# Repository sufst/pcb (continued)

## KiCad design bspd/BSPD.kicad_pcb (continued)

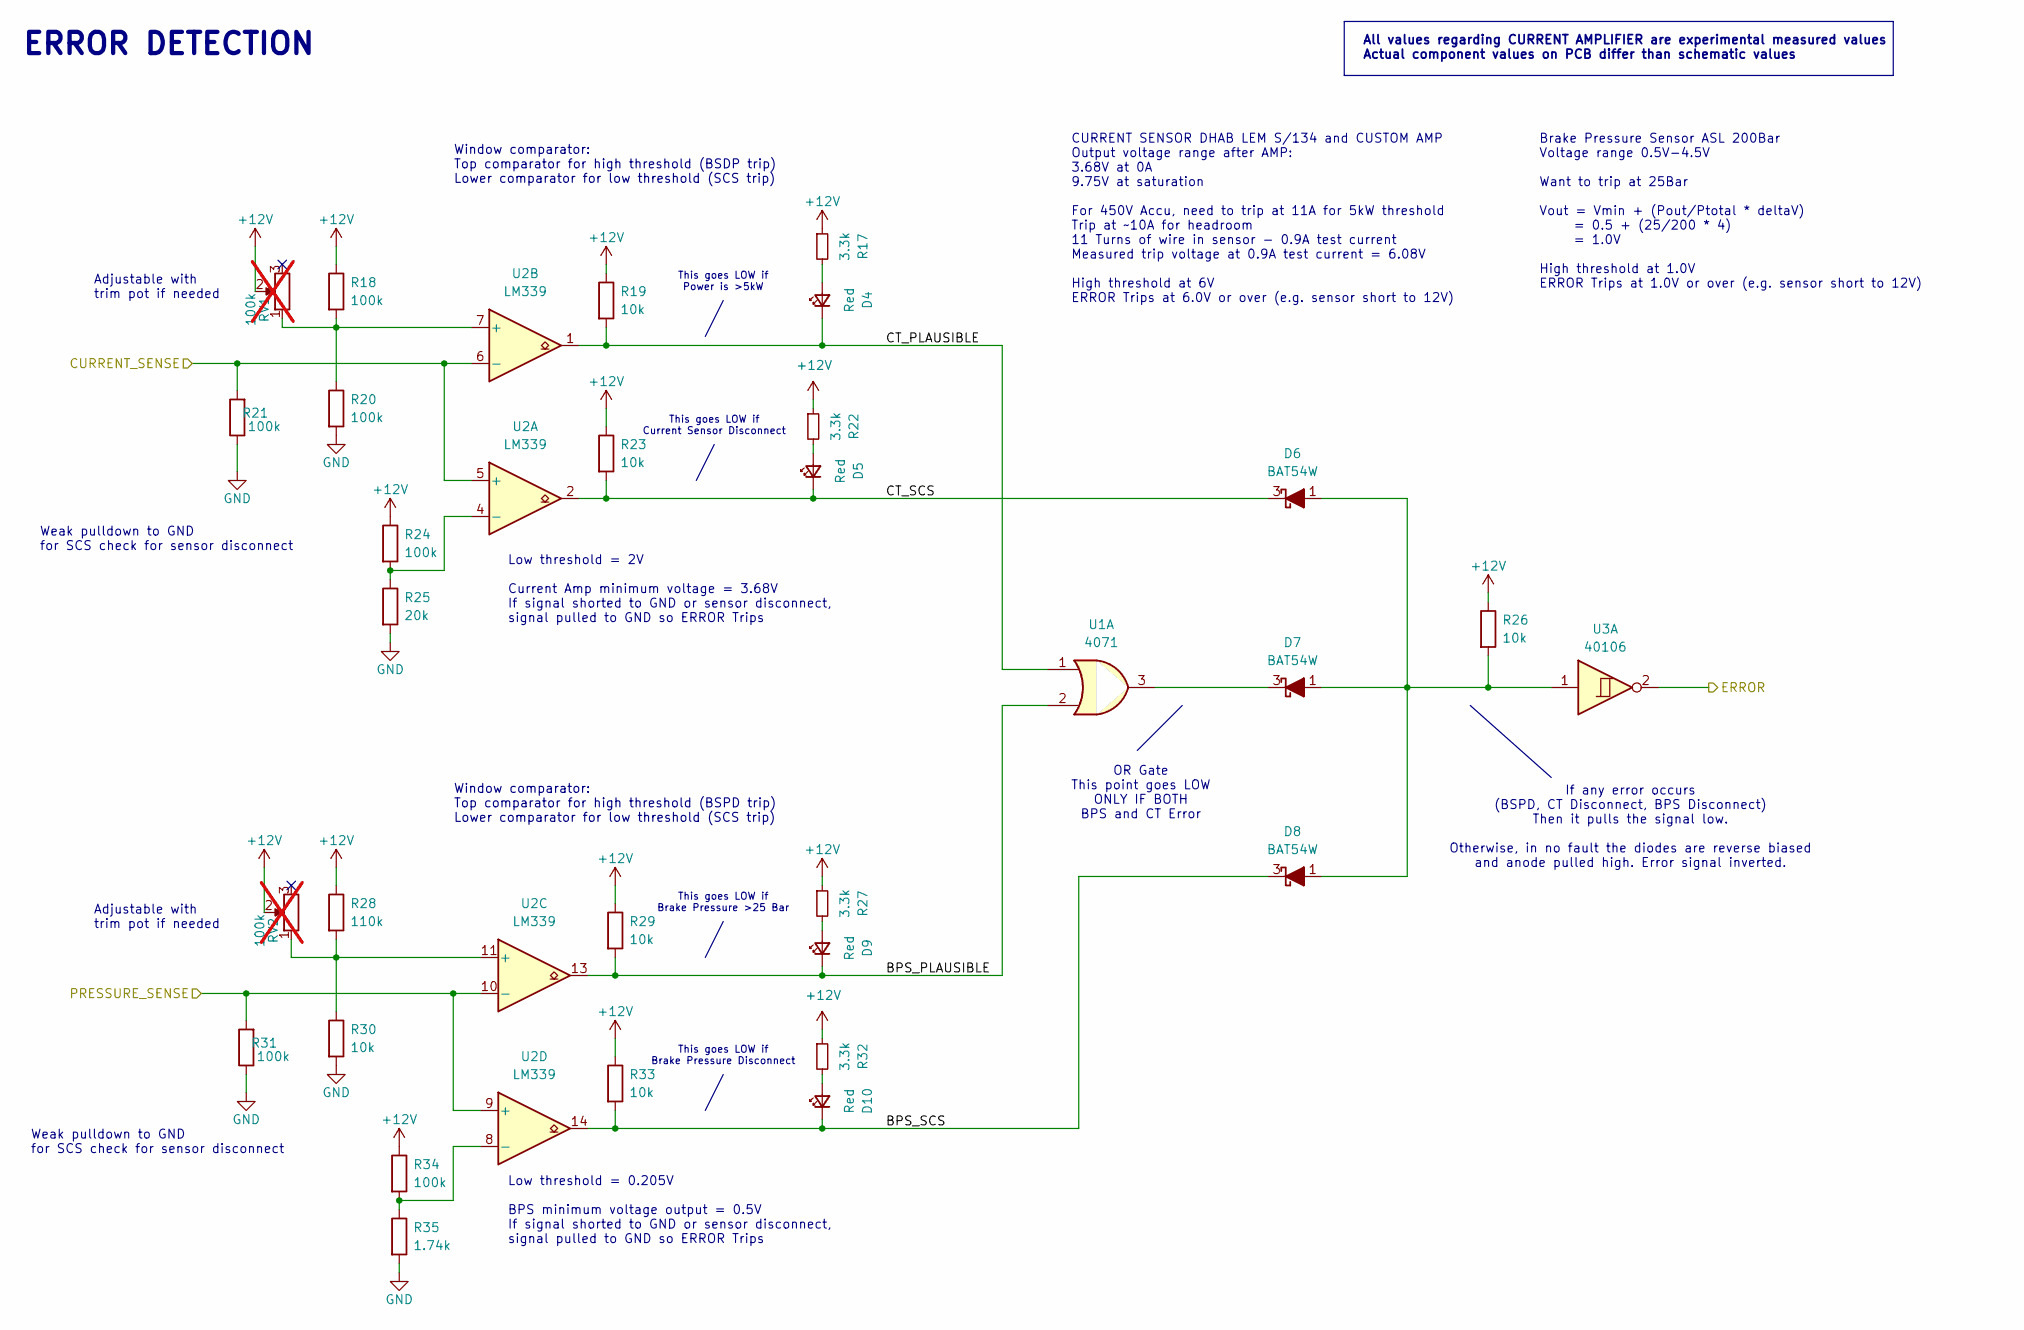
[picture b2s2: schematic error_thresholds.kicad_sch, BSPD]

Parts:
D4, D5, D9, D10: Red; LED_0603_1608Metric
D6, D7, D8: BAT54W; SOT-323_SC-70
R17, R22, R27, R32: 3.3k; R_0603_1608Metric
R18: 100k; R_0603_1608Metric; Mouser Part Number 603-RT0603FRE072K7L
R19, R23, R26, R29, R33: 10k; R_0603_1608Metric
R20, R24, R34: 100k; R_0603_1608Metric; Mouser Part Number 603-RT0603FRD078K2L
R21, R31: 100k; R_0603_1608Metric
R25: 20k; R_0603_1608Metric
R28: 110k; R_0603_1608Metric; Mouser Part Number 603-RT0603FRE072K7L
R30: 10k; R_0603_1608Metric; Mouser Part Number 603-RT0603FRD078K2L
R35: 1.74k; R_0603_1608Metric
RV1, RV2: 100k; Potentiometer_Bourns_3266W_Vertical; not fitted
U1: 4071; SOIC-14_3.9x8.7mm_P1.27mm
U2: LM339; SOIC-14_3.9x8.7mm_P1.27mm
U3: 40106; SOIC-14_3.9x8.7mm_P1.27mm

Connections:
+12V: R17.1, R18.1, R19.1, R22.1, R23.1, R24.1, R26.1, R27.1, R28.1, R29.1, R32.1, R33.1, R34.1, RV1.2, RV2.2; also elsewhere on the board
/BPS_SIG: R31.2, U2.9 (+), U2.10 (-); also elsewhere on the board
/CT_SIG: R21.2, U2.5 (+), U2.6 (-); also elsewhere on the board
/Error Thresholds/BPS_PLAUSIBLE: D9.1 (K), R29.2, U1.2, U2.13
/Error Thresholds/BPS_SCS: D8.3 (K), D10.1 (K), R33.2, U2.14
/Error Thresholds/CT_PLAUSIBLE: D4.1 (K), R19.2, U1.1, U2.1
/Error Thresholds/CT_SCS: D5.1 (K), D6.3 (K), R23.2, U2.2
/Error Thresholds/ERROR: U3.2; also elsewhere on the board
GND: R20.2, R21.1, R25.2, R30.2, R31.1, R35.2; also elsewhere on the board
unnamed: D4.2 (A), R17.2
unnamed: D5.2 (A), R22.2
unnamed: D6.1 (A), D7.1 (A), D8.1 (A), R26.2, U3.1
unnamed: D7.3 (K), U1.3
unnamed: D9.2 (A), R27.2
unnamed: D10.2 (A), R32.2
unnamed: R24.2, R25.1, U2.4 (-)
unnamed: R18.2, R20.1, RV1.1, U2.7 (+)
unnamed: R28.2, R30.1, RV2.1, U2.11 (+)
unnamed: R34.2, R35.1, U2.8 (-)

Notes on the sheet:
ERROR DETECTION
Low threshold = 0.205V BPS minimum voltage output = 0.5V If signal shorted to GND or sensor disconnect, signal pulled to GND so ERROR Trips
Low threshold = 2V Current Amp minimum voltage = 3.68V If signal shorted to GND or sensor disconnect, signal pulled to GND so ERROR Trips
OR Gate This point goes LOW ONLY IF BOTH BPS and CT Error
Window comparator: Top comparator for high threshold (BSPD trip) Lower comparator for low threshold (SCS trip)
All values regarding CURRENT AMPLIFIER are experimental measured values Actual component values on PCB differ than schematic values
Weak pulldown to GND for SCS check for sensor disconnect
This goes LOW if Power is >5kW
Window comparator: Top comparator for high threshold (BSDP trip) Lower comparator for low threshold (SCS trip)
CURRENT SENSOR DHAB LEM S/134 and CUSTOM AMP Output voltage range after AMP: 3.68V at 0A 9.75V at saturation For 450V Accu, need to trip at 11A for 5kW threshold Trip at ~10A for headroom 11 Turns of wire in sensor - 0.9A test current Measured trip voltage at 0.9A test current = 6.08V High threshol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
This goes LOW if Current Sensor Disconnect
Adjustable with trim pot if needed
If any error occurs (BSPD, CT Disconnect, BPS Disconnect) Then it pulls the signal low. Otherwise, in no fault the diodes are reverse biased and anode pulled high. Error signal inverted.
Brake Pressure Sensor ASL 200Bar Voltage range 0.5V-4.5V Want to trip at 25Bar Vout = Vmin + (Pout/Ptotal * deltaV) = 0.5 + (25/200 * 4) = 1.0V High threshold at 1.0V ERROR Trips at 1.0V or over (e.g. sensor short to 12V)
This goes LOW if Brake Pressure Disconnect
This goes LOW if Brake Pressure >25 Bar

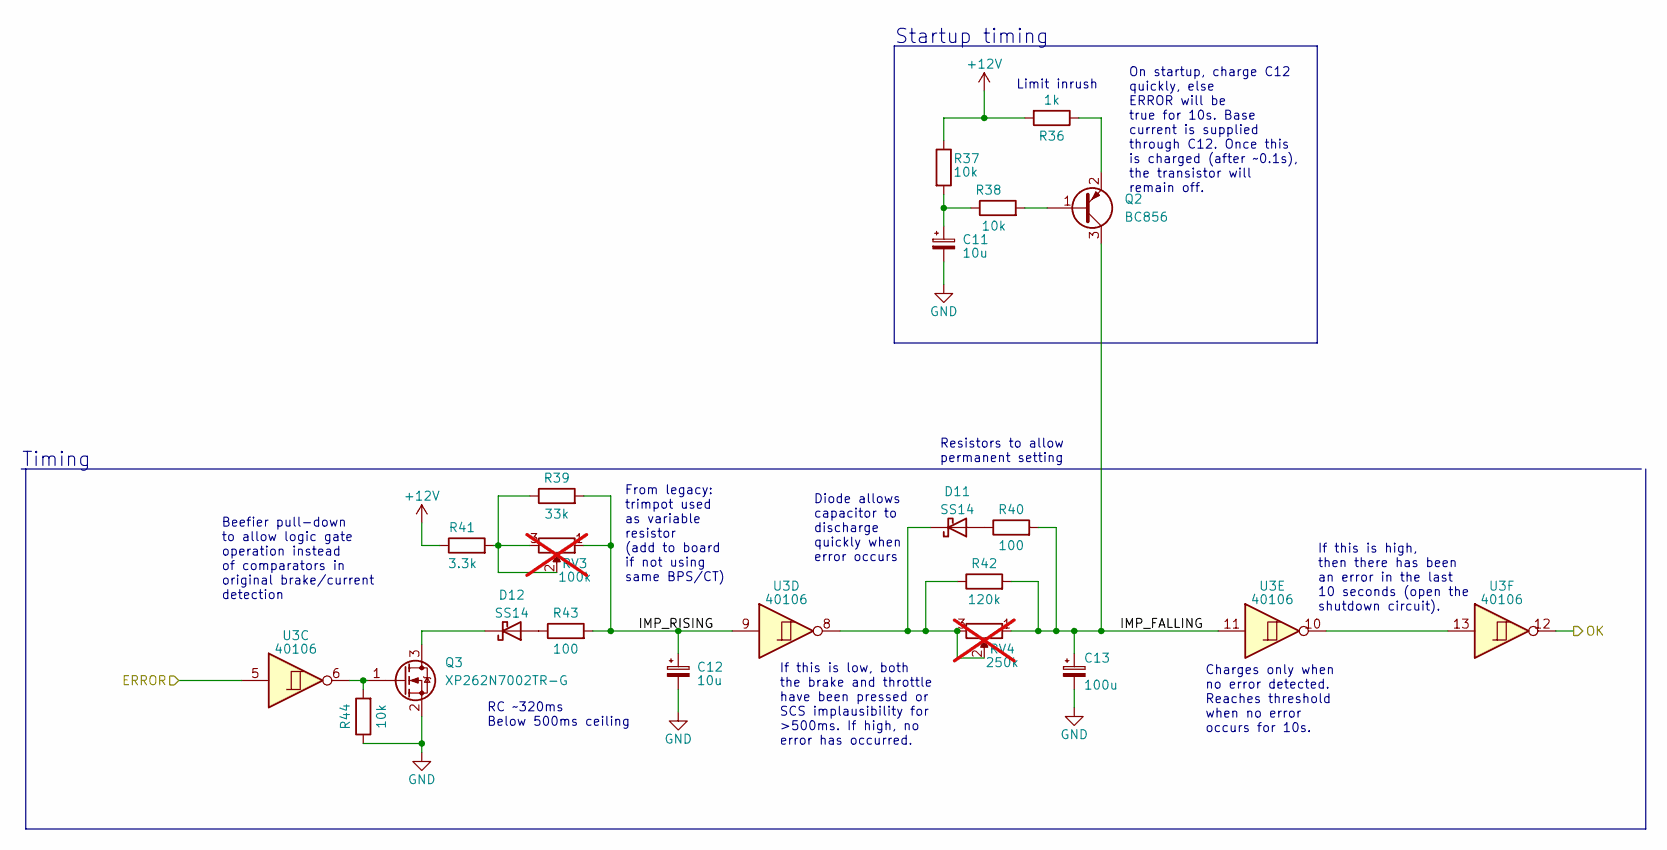
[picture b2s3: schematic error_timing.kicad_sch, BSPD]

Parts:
C11, C12: 10u; CP_Radial_D5.0mm_P2.00mm
C13: 100u; CP_Radial_D5.0mm_P2.00mm
D11, D12: SS14; D_SMA
Q2: BC856; SOT-23
Q3: XP262N7002TR-G; SOT-23
R36: 1k; R_0603_1608Metric
R37, R38, R44: 10k; R_0603_1608Metric
R39: 33k; R_0603_1608Metric; Mouser Part Number 603-RT0603FRE0733KL
R40, R43: 100; R_0603_1608Metric; Mouser Part Number 603-RT0603FRE07100RL
R41: 3.3k; R_0603_1608Metric
R42: 120k; R_0603_1608Metric
RV3: 100k; Potentiometer_Bourns_3266W_Vertical; not fitted
RV4: 250k; Potentiometer_Bourns_3266W_Vertical; not fitted
U3: 40106; SOIC-14_3.9x8.7mm_P1.27mm

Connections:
+12V: R36.2, R37.1, R41.1; also elsewhere on the board
/Error Thresholds/ERROR: U3.5; also elsewhere on the board
/Error Timing/IMP_FALLING: C13.1, Q2.3 (C), R40.2, R42.2, RV4.1, U3.11
/Error Timing/IMP_RISING: C12.1, R39.2, R43.2, RV3.1, U3.9
/Error Timing/OK: U3.12; also elsewhere on the board
GND: C11.2, C12.2, C13.2, Q3.2 (S), R44.1; also elsewhere on the board
unnamed: C11.1, R37.2, R38.1
unnamed: D11.2 (A), R40.1
unnamed: D11.1 (K), R42.1, RV4.2, RV4.3, U3.8
unnamed: D12.2 (A), R43.1
unnamed: D12.1 (K), Q3.3 (D)
unnamed: Q2.1 (B), R38.2
unnamed: Q2.2 (E), R36.1
unnamed: Q3.1 (G), R44.2, U3.6
unnamed: R39.1, R41.2, RV3.2, RV3.3
unnamed: U3.10, U3.13

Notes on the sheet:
Resistors to allow permanent setting
From legacy: trimpot used as variable resistor (add to board if not using same BPS/CT)
If this is low, both the brake and throttle have been pressed or SCS implausibility for >500ms. If high, no error has occurred.
Charges only when no error detected. Reaches threshold when no error occurs for 10s.
On startup, charge C12 quickly, else ERROR will be true for 10s. Base current is supplied through C12. Once this is charged (after ~0.1s), the transistor will remain off.
Limit inrush
Timing
RC ~320ms Below 500ms ceiling
Startup timing
If this is high, then there has been an error in the last 10 seconds (open the shutdown circuit).
Beefier pull-down to allow logic gate operation instead of comparators in original brake/current detection
Diode allows capacitor to discharge quickly when error occurs

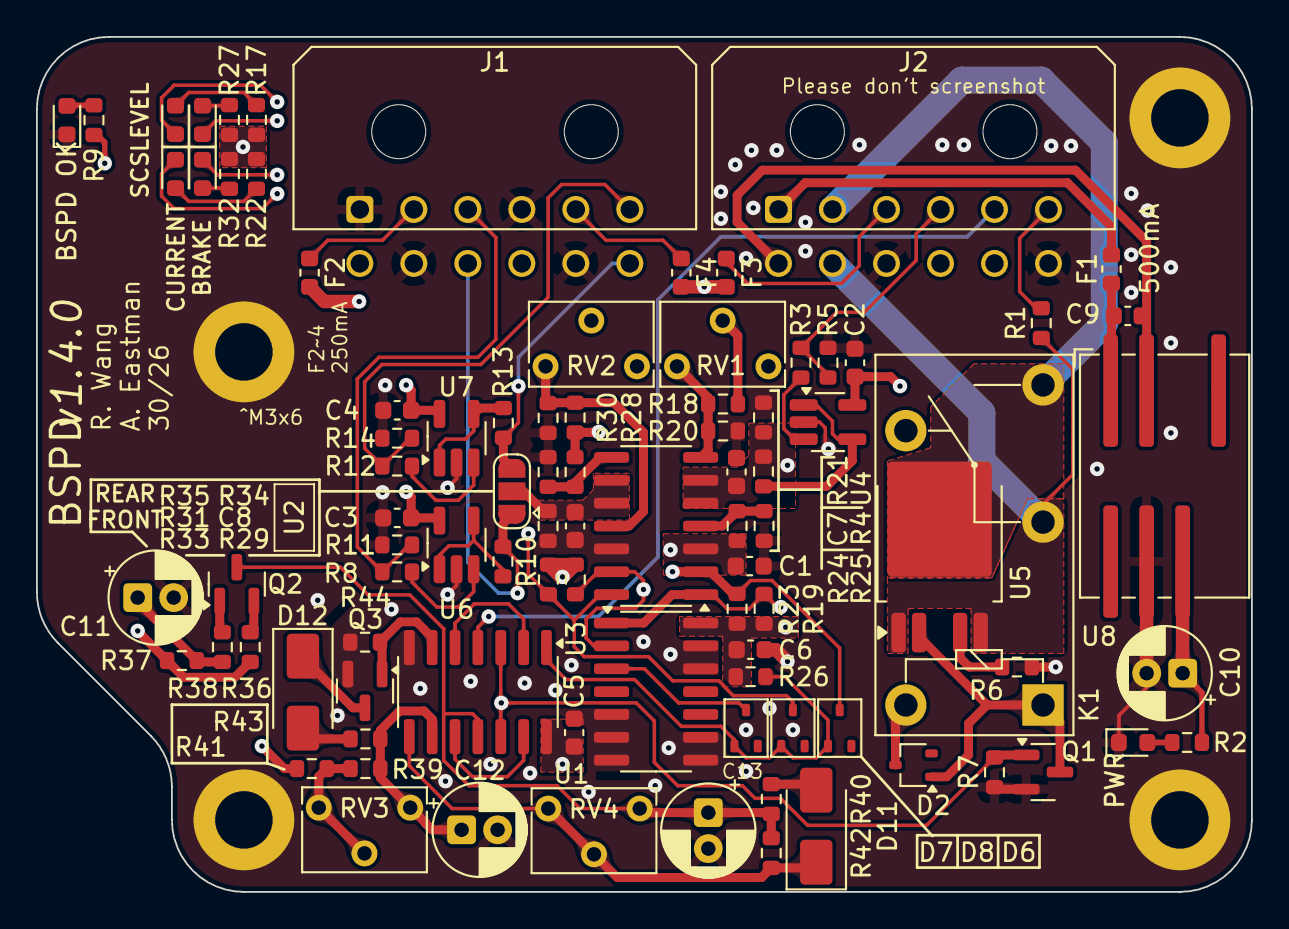
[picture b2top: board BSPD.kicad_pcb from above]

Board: 4 copper layers, 67.5 x 47.5 mm, 94 parts (0 on the bottom side), 57 nets.

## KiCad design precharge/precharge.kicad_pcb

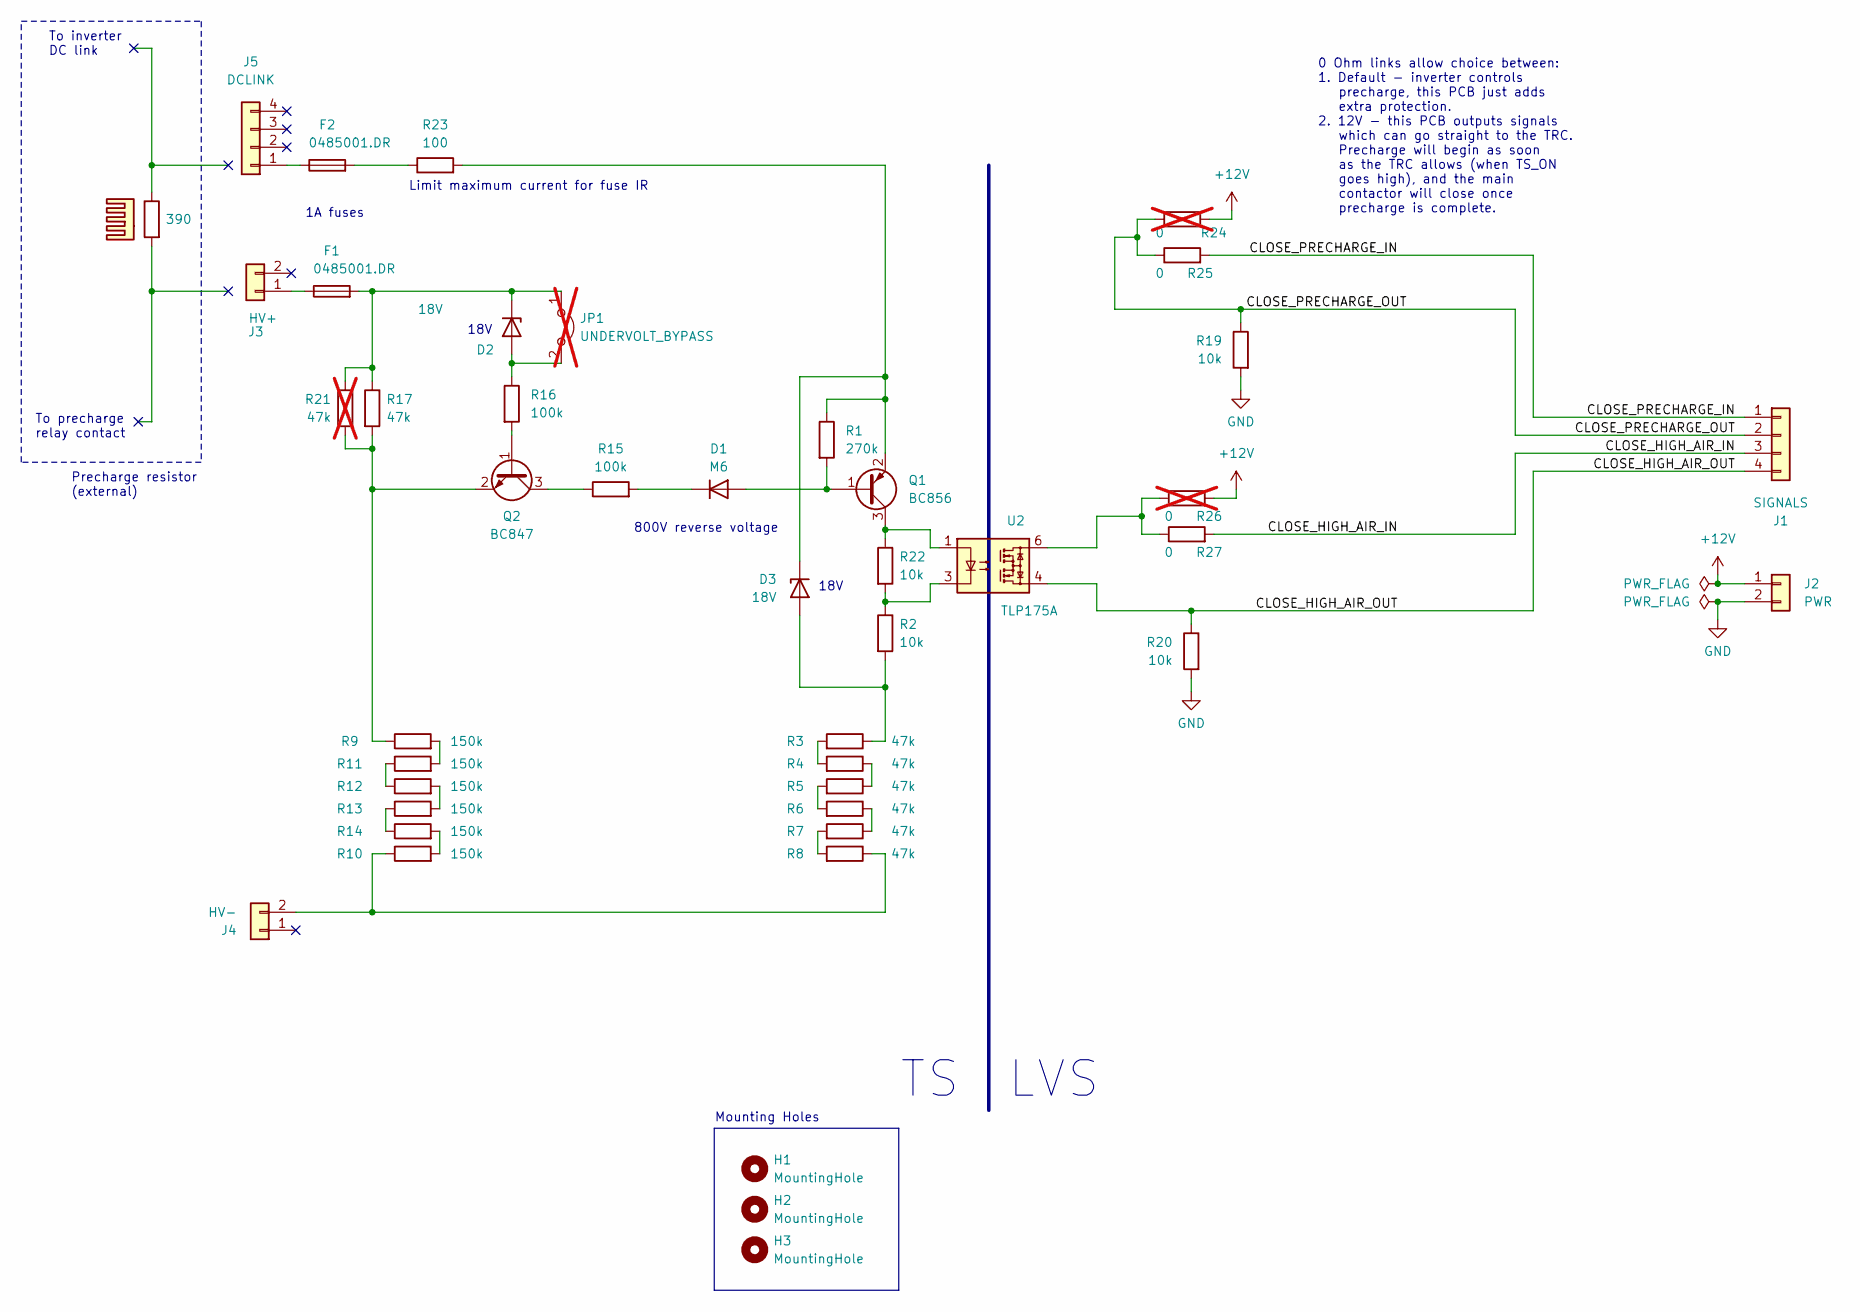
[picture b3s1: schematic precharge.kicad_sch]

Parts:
D1: M6; D_SMA_Handsoldering; MPN M6
D2, D3: 18V; D_SOD-123; MPN MMSZ5248B
F1, F2: 0485001.DR; Littelfuse-0485; MPN 0ACJ-1000-TE
H1, H2, H3: MountingHole; MountingHole_4.3mm_M4
HS1: Heatsink
J1: SIGNALS; Molex_Micro-Fit_3.0_43045-0412_2x02_P3.00mm_Vertical; MPN 43045-0412
J2: PWR; Molex_Micro-Fit_3.0_43045-0212_2x01_P3.00mm_Vertical; MPN 43045-0212
J3: HV+; Molex_Micro-Fit_3.0_43045-0212_2x01_P3.00mm_Vertical; MPN 43045-0412
J4: HV-; Molex_Micro-Fit_3.0_43045-0212_2x01_P3.00mm_Vertical; MPN 43045-0412
J5: DCLINK; Molex_Micro-Fit_3.0_43045-0412_2x02_P3.00mm_Vertical; MPN 43045-0412
JP1: UNDERVOLT_BYPASS; PinHeader_1x02_P2.54mm_Vertical; not fitted
Q1: BC856; SOT-23; MPN BC856A,215
Q2: BC847; SOT-23; MPN BC847A,215
R1: 270k; R_0805_2012Metric_Pad1.20x1.40mm_HandSolder; MPN AC0805FR-07270KL
R2, R19, R20, R22: 10k; R_0805_2012Metric_Pad1.20x1.40mm_HandSolder; MPN RT0603FRE1310KL
R3, R4, R5, R6, R7, R8: 47k; R_2512_6332Metric_Pad1.40x3.35mm_HandSolder; MPN RC2512FK-0747KL
R9, R10, R11, R12, R13, R14: 150k; R_0805_2012Metric_Pad1.20x1.40mm_HandSolder; MPN WR08X1503FTL
R15, R16: 100k; R_0805_2012Metric_Pad1.20x1.40mm_HandSolder; MPN RK73H2ATTDD1003F
R17: 47k; R_0805_2012Metric_Pad1.20x1.40mm_HandSolder; MPN AC0805FR-1347KL
R18: 390
R21: 47k; R_0805_2012Metric_Pad1.20x1.40mm_HandSolder; not fitted
R23: 100; R_0805_2012Metric_Pad1.20x1.40mm_HandSolder; MPN RC0805FR-13100RL
R24, R26: 0; R_0805_2012Metric_Pad1.20x1.40mm_HandSolder; not fitted
R25, R27: 0; R_0805_2012Metric_Pad1.20x1.40mm_HandSolder; MPN RC0805JR-130RL
U2: TLP175A; MFSOP6-4_4.4x3.6mm_P1.27mm; MPN TLP175A(TPLE

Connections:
+12V: J2.1, R24.2, R26.2
/CLOSE_HIGH_AIR_IN: J1.3, R27.2
/CLOSE_HIGH_AIR_OUT: J1.4, R20.1, U2.4
/CLOSE_PRECHARGE_IN: J1.1, R25.2
/CLOSE_PRECHARGE_OUT: J1.2, R19.1, R24.1, R25.1
GND: J2.2, R19.2, R20.2
unnamed: D1.2 (A), Q1.1 (B), R1.2
unnamed: D1.1 (K), R15.2
unnamed: D2.2 (A), JP1.2 (B), R16.1
unnamed: D2.1 (K), F1.2, JP1.1 (A), R17.1, R21.1
unnamed: D3.2 (A), R2.2, R3.1
unnamed: D3.1 (K), Q1.2 (E), R1.1, R23.2
unnamed: F2.2, R23.1
unnamed: F1.1, J3.1
unnamed: J4.2, R8.1, R10.1
unnamed: F2.1, J5.1
unnamed: Q1.3 (C), R22.1, U2.1
unnamed: Q2.1 (B), R16.2
unnamed: Q2.3 (C), R15.1
unnamed: Q2.2 (E), R9.1, R17.2, R21.2
unnamed: R2.1, R22.2, U2.3
unnamed: R3.2, R4.2
unnamed: R4.1, R5.1
unnamed: R5.2, R6.2
unnamed: R6.1, R7.1
unnamed: R7.2, R8.2
unnamed: R10.2, R14.2
unnamed: R11.1, R12.1
unnamed: R9.2, R11.2
unnamed: R12.2, R13.2
unnamed: R13.1, R14.1
unnamed: R26.1, R27.1, U2.6

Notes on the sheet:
18V
0 Ohm links allow choice between: 1. Default - inverter controls precharge, this PCB just adds extra protection. 2. 12V - this PCB outputs signals which can go straight to the TRC. Precharge will begin as soon as the TRC allows (when TS_ON goes high), and the main contactor will close once precharg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
To precharge relay contact
LVS
Mounting Holes
To inverter DC link
Precharge resistor (external)
Limit maximum current for fuse IR
800V reverse voltage
1A fuses

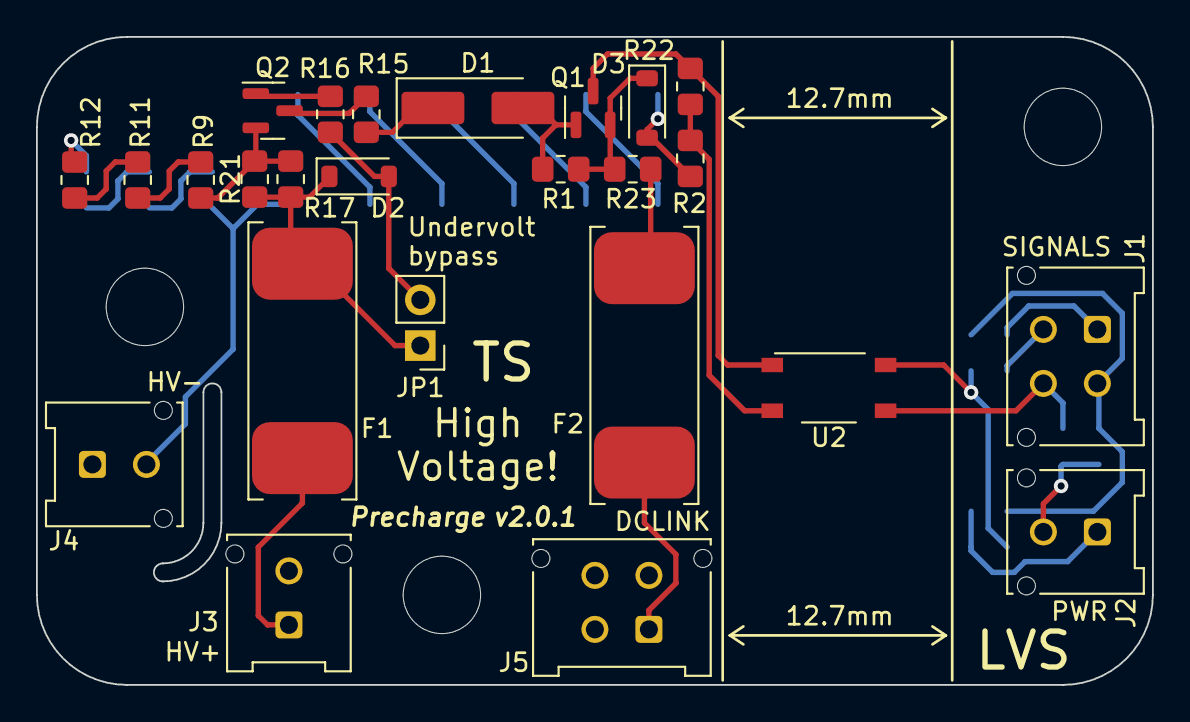
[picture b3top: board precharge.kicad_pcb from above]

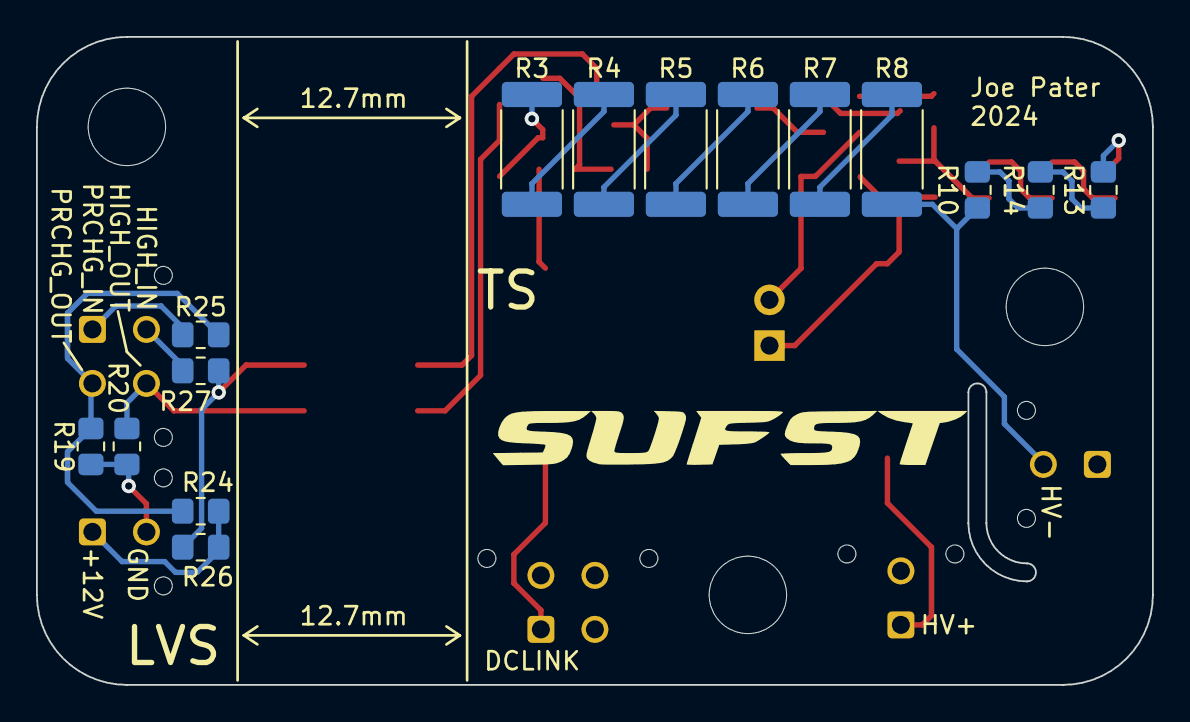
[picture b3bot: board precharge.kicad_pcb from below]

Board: 2 copper layers, 62.0 x 36.0 mm, 43 parts (15 on the bottom side), 32 nets.

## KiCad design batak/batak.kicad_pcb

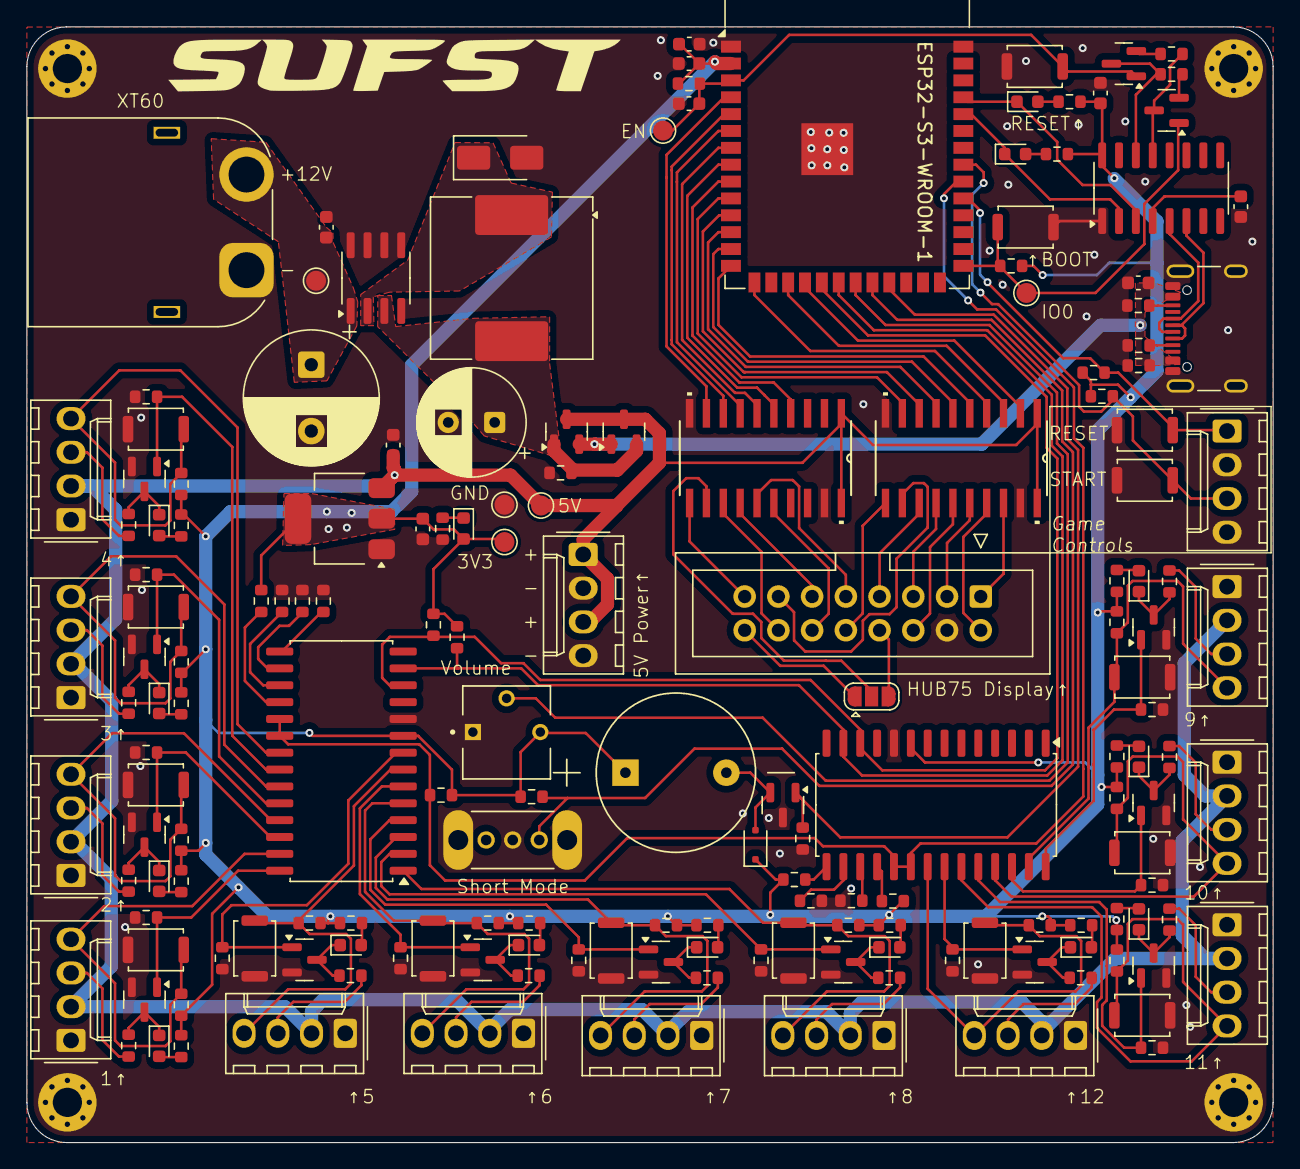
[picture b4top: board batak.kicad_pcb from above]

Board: 2 copper layers, 93.9 x 84.0 mm, 175 parts (0 on the bottom side), 130 nets.

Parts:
BZ1: Buzzer; CUI_CMI-1275-85T
C1, C3, C5, C8, C10, C11: 10uF; C_0603_1608Metric
C2, C4, C6: 100nF; C_0603_1608Metric
C7: 470uF; CP_Radial_D10.0mm_P5.00mm
C9: 180uF; CP_Radial_D8.0mm_P3.50mm
D1, D2, D3, D4, D5, D6, D7, D8, D9, D10, D11, D12, D14: GREEN; LED_0603_1608Metric
D13: YELLOW; LED_0603_1608Metric
D15: 1N5817; D_SOD-323F
D16: RED; LED_0603_1608Metric
D17: SS34; D_SMA
H1, H2, H3, H4: MountingHole_Pad; MountingHole_2.2mm_M2_Pad_Via
J1: XT60; AMASS_XT60PW-M_1x02_P7.20mm_Horizontal
J2, J3, J4, J5, J6, J7, J8, J9, J10, J11, J12, J13, J14, J17: Molex_KK-254; Molex_KK-254_AE-6410-04A_1x04_P2.54mm_Vertical
J15: USB_C_Receptacle_USB2.0_16P; USB_C_Receptacle_GCT_USB4105-xx-A_16P_TopMnt_Horizontal
J16: Conn_02x08_Odd_Even; IDC-Header_2x08_P2.54mm_Vertical
JP1: SolderJumper_3_Open; SolderJumper-3_P1.3mm_Open_RoundedPad1.0x1.5mm
L1: 68uH; L_Coilcraft_MSS1210-XXX
Q1, Q2, Q3, Q4, Q5, Q6, Q7, Q8, Q9, Q10, Q11, Q12, Q13: AO3400A; SOT-23
Q14, Q17: AO3401A; SOT-23
Q15, Q16: NPN; SOT-23
R1, R2, R3, R4, R5, R6, R9, R10, R13, R14, R17, R18, R21, R22, R25, R26, R27, R28, R29, R30, R31, R32, R33, R34, R35, R38, R39, R42, R43, R46, R47, R50, R51, R54, R55, R58, R59, R62, R64, R65, R72: 10k; R_0603_1608Metric
R7, R11, R15, R19, R23, R36, R40, R44, R48, R52, R56, R60, R66, R67, R71: 1k; R_0603_1608Metric
R8, R12, R16, R20, R24, R37, R41, R45, R49, R53, R57, R61: 0Ω; R_0603_1608Metric
R63, R70: 100k; R_0603_1608Metric
R68, R69, R73, R74: 5.1k; R_0603_1608Metric
RV1: 300k; TRIM_3362P-1-304LF
SW1: 0S102011MS2QN1
SW2: GAME_RESET; SW_Push_SPST_NO_Alps_SKRK
SW3: GAME_START; SW_Push_SPST_NO_Alps_SKRK
SW4, SW5, SW6, SW7, SW8, SW9, SW10, SW11, SW12, SW13, SW14, SW15: BUTTON; SW_Push_SPST_NO_Alps_SKRK
SW16: BOOT; SW_Push_SPST_NO_Alps_SKRK
SW17: RESET; SW_Push_SPST_NO_Alps_SKRK
TP1: GND; TestPoint_Pad_D1.5mm
TP2: +3V3; TestPoint_Pad_D1.5mm
TP3: +5V; TestPoint_Pad_D1.5mm
TP4: +12V; TestPoint_Pad_D1.5mm
TP5: IO0; TestPoint_Pad_D1.5mm
TP6: EN; TestPoint_Pad_D1.5mm
U1: ESP32-S3-WROOM-1
U2, U3: MCP23017_SO; SOIC-28W_7.5x17.9mm_P1.27mm
U4: CH340C; SOIC-16_3.9x9.9mm_P1.27mm
U5: XL1509-5.0; SOIC-8_3.9x4.9mm_P1.27mm
U6: AZ1117CH-3.3TRG1; SOT-223-3_TabPin2
U7, U8: SN74AHCT245NSR; NS20

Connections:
+3V3: BZ1.1 (+), C2.1, C3.2, C5.1, C11.2, D15.1 (K), D16.2 (A), R1.1, R2.2, R3.2, R4.2, R5.2, R7.2, R9.2, R11.2, R13.2, R15.2, R17.2, R19.2, R21.2, R23.2, R25.2, R26.2, R32.2, R33.2, R34.2, R36.2, R38.2, R40.2, R42.2, R44.2, R46.2, R48.2, R50.2, R52.2, R54.2, R56.2, R58.2, R60.2, R62.2, R66.2, R67.2, R73.1, R74.1, RV1.3, TP2.1, U1.2 (3V3), U2.9 (VDD), U3.9 (VDD), U4.16 (VCC), U6.2 (VO)
+5V: C10.2, J3.2, J4.2, J5.2, J6.2, J7.2, J8.2, J9.2, J10.2, J11.2, J12.2, J13.2, J14.2, J17.1, J17.3, Q14.3 (D), Q17.3 (D), TP3.1, U6.3 (VI), U7.1 (DIR), U7.20 (VCC), U8.1 (DIR), U8.20 (VCC)
+12V: C7.1, C8.1, J1.2, TP4.1, U5.1 (VIN)
/ADDRA_3V: U1.8 (IO15), U8.5 (A4)
/ADDRB_3V: U1.10 (IO17), U7.9 (A8)
/ADDRC_3V: U1.7 (IO7), U8.6 (A5)
/ADDRD_3V: U1.9 (IO16), U8.4 (A3)
/ADDRE_3V: U1.5 (IO5), U8.8 (A7)
/Arcade Button Array + Multiplexers/BTN_1_LIGHT: Q2.1 (G), R6.2, U2.28 (GPA7)
/Arcade Button Array + Multiplexers/BTN_1_OUTPUT: J3.4, R9.1, SW4.2, U2.27 (GPA6)
/Arcade Button Array + Multiplexers/BTN_2_LIGHT: Q3.1 (G), R10.2, U2.26 (GPA5)
/Arcade Button Array + Multiplexers/BTN_2_OUTPUT: J4.4, R13.1, SW5.2, U2.25 (GPA4)
/Arcade Button Array + Multiplexers/BTN_3_LIGHT: Q4.1 (G), R14.2, U2.24 (GPA3)
/Arcade Button Array + Multiplexers/BTN_3_OUTPUT: J5.4, R17.1, SW6.2, U2.23 (GPA2)
/Arcade Button Array + Multiplexers/BTN_4_LIGHT: Q5.1 (G), R18.2, U2.22 (GPA1)
/Arcade Button Array + Multiplexers/BTN_4_OUTPUT: J6.4, R21.1, SW7.2, U2.21 (GPA0)
/Arcade Button Array + Multiplexers/BTN_5_LIGHT: Q6.1 (G), R22.2, U2.8 (GPB7)
/Arcade Button Array + Multiplexers/BTN_5_OUTPUT: J7.4, R25.1, SW8.2, U2.7 (GPB6)
/Arcade Button Array + Multiplexers/BTN_6_LIGHT: Q7.1 (G), R35.2, U2.6 (GPB5)
/Arcade Button Array + Multiplexers/BTN_6_OUTPUT: J8.4, R38.1, SW9.2, U2.5 (GPB4)
/Arcade Button Array + Multiplexers/BTN_7_LIGHT: Q8.1 (G), R39.2, U2.4 (GPB3)
/Arcade Button Array + Multiplexers/BTN_7_OUTPUT: J9.4, R42.1, SW10.2, U2.3 (GPB2)
/Arcade Button Array + Multiplexers/BTN_8_LIGHT: Q9.1 (G), R43.2, U2.2 (GPB1)
/Arcade Button Array + Multiplexers/BTN_8_OUTPUT: J10.4, R46.1, SW11.2, U2.1 (GPB0)
/Arcade Button Array + Multiplexers/BTN_9_LIGHT: Q10.1 (G), R47.2, U3.28 (GPA7)
/Arcade Button Array + Multiplexers/BTN_9_OUTPUT: J11.4, R50.1, SW12.2, U3.27 (GPA6)
/Arcade Button Array + Multiplexers/BTN_10_LIGHT: Q11.1 (G), R51.2, U3.26 (GPA5)
/Arcade Button Array + Multiplexers/BTN_10_OUTPUT: J12.4, R54.1, SW13.2, U3.25 (GPA4)
/Arcade Button Array + Multiplexers/BTN_11_LIGHT: Q12.1 (G), R55.2, U3.24 (GPA3)
/Arcade Button Array + Multiplexers/BTN_11_OUTPUT: J13.4, R58.1, SW14.2, U3.23 (GPA2)
/Arcade Button Array + Multiplexers/BTN_12_LIGHT: Q13.1 (G), R59.2, U3.22 (GPA1)
/Arcade Button Array + Multiplexers/BTN_12_OUTPUT: J14.4, R62.1, SW15.2, U3.21 (GPA0)
/Auto reset/DTR: Q15.3 (E), R65.1, U4.13 (~DTR)
/Auto reset/RTS: Q16.3 (E), R64.1, U4.14 (~RTS)
/B1_3V: U1.15 (IO3), U7.4 (A3)
/B2_3V: U1.12 (IO8), U7.7 (A6)
/BUCK5V: C9.1, L1.2, Q14.2 (S), Q17.1 (G), R70.1, U5.3 (FB)
/BUZZER: Q1.1 (G), R72.2, U1.23 (IO21)
/CLK_3V: U1.11 (IO18), U7.8 (A7)
/EN: C1.2, Q16.1 (C), R3.1, SW17.1, TP6.1, U1.3 (EN)
/G1_3V: U1.17 (IO9), U7.3 (A2)
/G2_3V: U1.14 (IO20), U7.5 (A4)
/GAME_RESET: J2.1, R5.1, SW2.1, U1.31 (IO38)
/GAME_START: J2.3, R4.1, SW3.1, U1.33 (IO40)
/INT: R26.1, U1.32 (IO39), U2.19 (INTB), U2.20 (INTA), U3.19 (INTB), U3.20 (INTA)
/IO0: Q15.1 (C), R2.1, SW16.1, TP5.1, U1.27 (IO0)
/LAT_3V: U1.6 (IO6), U8.7 (A6)
/OE_3V: U1.4 (IO4), U8.9 (A8)
/P5 Display Connector + Level shifter/CLK: J16.13, U7.12 (B7)
/P5 Display Connector + Level shifter/LAT: J16.14, U8.13 (B6)
/P5 Display Connector + Level shifter/M1_A: J16.9, U8.15 (B4)
/P5 Display Connector + Level shifter/M1_B: J16.10, U7.11 (B8)
/P5 Display Connector + Level shifter/M1_B1: J16.3, U7.16 (B3)
/P5 Display Connector + Level shifter/M1_B2: J16.7, U7.13 (B6)
/P5 Display Connector + Level shifter/M1_C: J16.11, U8.14 (B5)
/P5 Display Connector + Level shifter/M1_D: J16.12, U8.16 (B3)
/P5 Display Connector + Level shifter/M1_E: JP1.2 (C), U8.12 (B7)
/P5 Display Connector + Level shifter/M1_E8: J16.8, JP1.3 (B)
/P5 Display Connector + Level shifter/M1_E16: J16.16, JP1.1 (A)
/P5 Display Connector + Level shifter/M1_G1: J16.2, U7.17 (B2)
/P5 Display Connector + Level shifter/M1_G2: J16.6, U7.15 (B4)
/P5 Display Connector + Level shifter/M1_R1: J16.1, U7.18 (B1)
/P5 Display Connector + Level shifter/M1_R2: J16.5, U7.14 (B5)
/P5 Display Connector + Level shifter/OE: J16.15, U8.11 (B8)
/R1_3V: U1.18 (IO10), U7.2 (A1)
/R2_3V: U1.13 (IO19), U7.6 (A5)
/RX0: D13.1 (K), U1.36 (RXD0), U4.2 (TXD)
/SCL: R74.2, U1.19 (IO11), U2.12 (SCK), U3.12 (SCK)
/SDA: R73.2, U1.20 (IO12), U2.13 (SDA), U3.13 (SDA)
/TOGGLE_SW: R1.2, SW1.3 (C), U1.22 (IO14)
/TX0: D14.1 (K), U1.37 (TXD0), U4.3 (RXD)
/USB5V: C6.2, J15.A4 (VBUS), J15.A9 (VBUS), J15.B4 (VBUS), J15.B9 (VBUS), Q14.1 (G), Q17.2 (S), R63.1
/USB to UART converter/USB_D+: J15.A6 (D+), J15.B6 (D+), U4.5 (UD+)
/USB to UART converter/USB_D-: J15.A7 (D-), J15.B7 (D-), U4.6 (UD-)
/VOLUME_POT: RV1.2, U1.21 (IO13)
GND: C1.1, C2.2, C3.1, C4.2, C5.2, C6.1, C7.2, C8.2, C9.2, C10.1, C11.1, D17.2 (A), H1.1, H2.1, H3.1, H4.1, J1.1, J2.2, J2.4, J3.1, J4.1, J5.1, J6.1, J7.1, J8.1, J9.1, J10.1, J11.1, J12.1, J13.1, J14.1, J15.A1 (GND), J15.A12 (GND), J15.B1 (GND), J15.B12 (GND), J15.S1 (SHIELD), J16.4, J17.2, J17.4, Q1.3 (D), Q2.2 (S), Q3.2 (S), Q4.2 (S), Q5.2 (S), Q6.2 (S), Q7.2 (S), Q8.2 (S), Q9.2 (S), Q10.2 (S), Q11.2 (S), Q12.2 (S), Q13.2 (S), R6.1, R10.1, R14.1, R18.1, R22.1, R27.2, R28.2, R29.2, R30.2, R31.2, R35.1, R39.1, R43.1, R47.1, R51.1, R55.1, R59.1, R63.2, R68.1, R69.1, R70.2, R71.2, R72.1, RV1.1, SW1.2 (B), SW1.4 (BASE), SW1.5 (BASE), SW2.2, SW3.2, SW4.1, SW5.1, SW6.1, SW7.1, SW8.1, SW9.1, SW10.1, SW11.1, SW12.1, SW13.1, SW14.1, SW15.1, SW16.2, SW17.2, TP1.1, U1.1 (GND), U1.40 (GND), U1.41 (GND), U2.10 (VSS), U3.10 (VSS), U4.1 (GND), U5.4 (~EN), U5.5 (GND), U5.6 (GND), U5.7 (GND), U5.8 (GND), U6.1 (GND), U7.10 (GND), U7.19 (*OE), U8.10 (GND), U8.19 (*OE)
unnamed: BZ1.2 (-), D15.2 (A), Q1.2 (S)
unnamed: D1.2 (A), R7.1
unnamed: D1.1 (K), Q2.3 (D), R8.1
unnamed: D2.2 (A), R11.1
unnamed: D2.1 (K), Q3.3 (D), R12.1
unnamed: D3.2 (A), R15.1
unnamed: D3.1 (K), Q4.3 (D), R16.1
unnamed: D4.2 (A), R19.1
unnamed: D4.1 (K), Q5.3 (D), R20.1
unnamed: D5.2 (A), R23.1
unnamed: D5.1 (K), Q6.3 (D), R24.1
unnamed: D6.2 (A), R36.1
unnamed: D6.1 (K), Q7.3 (D), R37.1
unnamed: D7.2 (A), R40.1
unnamed: D7.1 (K), Q8.3 (D), R41.1
unnamed: D8.2 (A), R44.1
unnamed: D8.1 (K), Q9.3 (D), R45.1
unnamed: D9.2 (A), R48.1
unnamed: D9.1 (K), Q10.3 (D), R49.1
unnamed: D10.2 (A), R52.1
unnamed: D10.1 (K), Q11.3 (D), R53.1
unnamed: D11.2 (A), R56.1
unnamed: D11.1 (K), Q12.3 (D), R57.1
unnamed: D12.2 (A), R60.1
unnamed: D12.1 (K), Q13.3 (D), R61.1
unnamed: D13.2 (A), R66.1
unnamed: D14.2 (A), R67.1
unnamed: D16.1 (K), R71.1
unnamed: D17.1 (K), L1.1, U5.2 (OUT)
unnamed: J3.3, R8.2
unnamed: J4.3, R12.2
unnamed: J5.3, R16.2
unnamed: J6.3, R20.2
unnamed: J7.3, R24.2
unnamed: J8.3, R37.2
unnamed: J9.3, R41.2
unnamed: J10.3, R45.2
unnamed: J11.3, R49.2
unnamed: J12.3, R53.2
unnamed: J13.3, R57.2
unnamed: J14.3, R61.2
unnamed: J15.A5 (CC1), R69.2
unnamed: J15.B5 (CC2), R68.2
unnamed: Q15.2 (B), R64.2
unnamed: Q16.2 (B), R65.2
unnamed: R29.1, U2.15 (A0)
unnamed: R28.1, U2.16 (A1)
unnamed: R27.1, U2.17 (A2)
unnamed: R33.1, U2.18 (~RESET)
unnamed: R32.1, U3.15 (A0)
unnamed: R31.1, U3.16 (A1)
unnamed: R30.1, U3.17 (A2)
unnamed: R34.1, U3.18 (~RESET)
unnamed: C4.1, U4.4 (V3)
